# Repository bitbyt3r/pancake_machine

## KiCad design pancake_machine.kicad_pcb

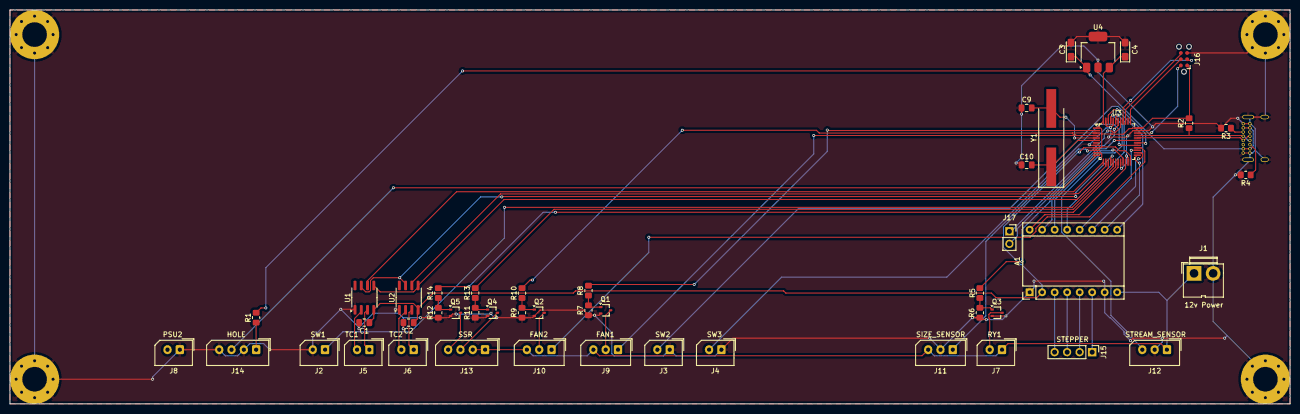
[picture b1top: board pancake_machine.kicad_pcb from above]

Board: 2 copper layers, 260.0 x 80.0 mm, 53 parts (1 on the bottom side), 60 nets.

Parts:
A1: Pololu_Breakout_A4988; Pololu_Breakout-16_15.2x20.3mm
C1, C2: 0.1uF; C_0805_2012Metric_Pad1.18x1.45mm_HandSolder
C3, C4: 10uF; CP_EIA-3216-10_Kemet-I_Pad1.58x1.35mm_HandSolder
C9, C10: 20pF; C_0805_2012Metric_Pad1.18x1.45mm_HandSolder
H2, H3, H4, H5: MountingHole_Pad; MountingHole_5mm_Pad_Via
J1: 12v Power; JWT_A3963_1x02_P3.96mm_Vertical
J2: SW1; Molex_SPOX_5267-02A_1x02_P2.50mm_Vertical
J3: SW2; Molex_SPOX_5267-02A_1x02_P2.50mm_Vertical
J4: SW3; Molex_SPOX_5267-02A_1x02_P2.50mm_Vertical
J5: TC1; Molex_SPOX_5267-02A_1x02_P2.50mm_Vertical
J6: TC2; Molex_SPOX_5267-02A_1x02_P2.50mm_Vertical
J7: RY1; Molex_SPOX_5267-02A_1x02_P2.50mm_Vertical
J8: PSU2; Molex_SPOX_5267-02A_1x02_P2.50mm_Vertical
J9: FAN1; Molex_SPOX_5267-03A_1x03_P2.50mm_Vertical
J10: FAN2; Molex_SPOX_5267-03A_1x03_P2.50mm_Vertical
J11: SIZE_SENSOR; Molex_SPOX_5267-03A_1x03_P2.50mm_Vertical
J12: STREAM_SENSOR; Molex_SPOX_5267-03A_1x03_P2.50mm_Vertical
J13: SSR; Molex_SPOX_5267-04A_1x04_P2.50mm_Vertical
J14: HOLE; Molex_SPOX_5267-04A_1x04_P2.50mm_Vertical
J15: Stepper; PinHeader_1x04_P2.54mm_Vertical
J16: Conn_ARM_SWD_TagConnect_TC2030; Tag-Connect_TC2030-IDC-NL_2x03_P1.27mm_Vertical
J17: Conn_01x02_Socket; PinSocket_1x02_P2.54mm_Vertical
J18: USB_C_Receptacle_USB2.0_14P; USB_C_Receptacle_GCT_USB4085
Q1, Q2, Q3, Q4, Q5: BSS214NW; SOT-323_SC-70
R1: 161; R_0805_2012Metric_Pad1.20x1.40mm_HandSolder
R2: 1k5; R_0805_2012Metric_Pad1.20x1.40mm_HandSolder
R3, R4: 5k1; R_0805_2012Metric_Pad1.20x1.40mm_HandSolder
R5, R8, R10, R13, R14: 100; R_0805_2012Metric_Pad1.20x1.40mm_HandSolder
R6, R7, R9, R11, R12: 100k; R_0805_2012Metric_Pad1.20x1.40mm_HandSolder
U1, U2: MAX31855KASA; SOIC-8_3.9x4.9mm_P1.27mm
U3: STM32F103CBTx; LQFP-48_7x7mm_P0.5mm
U4: LT1963AxST-3.3; SOT-223-3_TabPin2
Y1: 16MHz; Crystal_SMD_HC49-SD_HandSoldering

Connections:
+3.3V: A1.2 (VDD), C1.1, C2.1, C4.1, J16.1 (VCC), R2.2, U1.4 (V_CC), U2.4 (V_CC), U3.1 (VBAT), U3.9 (VDDA), U3.24 (VDD), U3.36 (VDD), U3.48 (VDD), U4.3 (OUT)
+5V: C3.1, J18.A4 (VBUS), J18.A9 (VBUS), J18.B4 (VBUS), J18.B9 (VBUS), R1.2, U4.1 (IN)
+12V: A1.8 (VMOT), J1.1, J7.1, J9.3, J10.3, J11.3, J12.1, J13.1, J13.2
BAG_DOOR_CLOSED: J2.1, U3.17 (PA7)
BELT_MOTOR: R5.1, U3.31 (PA10)
DIAG: J17.2, U3.42 (PB6)
DIR: A1.16 (DIR), U3.22 (PB11)
END_OF_TRAVEL: J3.2, U3.30 (PA9)
FAN1_PWR: R8.2, U3.2 (PC13)
FAN1_SPEED: J9.1, U3.4 (PC15)
FAN2_PWR: R10.2, U3.3 (PC14)
FAN2_SPEED: J10.1, U3.28 (PB15)
GND: A1.1 (GND), A1.7 (GND), C1.2, C2.2, C3.2, C4.2, C9.1, C10.1, H2.1, H3.1, H4.1, H5.1, J1.2, J2.2, J3.1, J4.1, J8.1, J11.2, J12.2, J14.2, J14.4, J16.5 (GND), J18.A1 (GND), J18.A12 (GND), J18.B1 (GND), J18.B12 (GND), J18.S1 (SHIELD), Q1.2 (S), Q2.2 (S), Q3.2 (S), Q4.2 (S), Q5.2 (S), R3.2, R4.2, R6.1, R7.1, R9.1, R11.1, R12.1, U1.1 (GND), U2.1 (GND), U3.8 (VSSA), U3.20 (PB2), U3.23 (VSS), U3.35 (VSS), U3.44 (BOOT0), U3.47 (VSS), U4.2 (GND)
HOLE: J14.3, U3.12 (PA2)
INDEX: J17.1, U3.41 (PB5)
JNTRST: J16.3 (~RESET), U3.40 (PB4)
LOWER_HEATER: R14.2, U3.19 (PB1)
MS1: A1.10 (MS1), U3.25 (PB12)
MS2: A1.11 (MS2), U3.26 (PB13)
MS3: A1.12 (MS3), U3.27 (PB14)
unnamed: A1.4 (1A), J15.3
unnamed: A1.3 (1B), J15.4
unnamed: A1.5 (2A), J15.2
unnamed: A1.6 (2B), J15.1
unnamed: J5.1, U1.3 (T+)
unnamed: J5.2, U1.2 (T-)
unnamed: J6.1, U2.3 (T+)
unnamed: J6.2, U2.2 (T-)
unnamed: J7.2, Q3.3 (D)
unnamed: J9.2, Q1.3 (D)
unnamed: J10.2, Q2.3 (D)
unnamed: J13.3, Q4.3 (D)
unnamed: J13.4, Q5.3 (D)
unnamed: J14.1, R1.1
unnamed: J18.A5 (CC1), R3.1
unnamed: J18.B5 (CC2), R4.1
unnamed: Q1.1 (G), R7.2, R8.1
unnamed: Q2.1 (G), R9.2, R10.1
unnamed: Q3.1 (G), R5.2, R6.2
unnamed: Q4.1 (G), R11.2, R13.1
unnamed: Q5.1 (G), R12.2, R14.1
unnamed: C9.2, U3.5 (PD0), Y1.2
unnamed: C10.2, U3.6 (PD1), Y1.1
SIZE: J11.1, U3.10 (PA0)
SPI_MISO: U1.7 (SO), U2.7 (SO), U3.16 (PA6)
SPI_SCK: U1.5 (SCK), U2.5 (SCK), U3.15 (PA5)
START_OF_TRAVEL: J4.2, U3.29 (PA8)
STEP: A1.15 (STEP), U3.21 (PB10)
STREAM: J12.3, U3.11 (PA1)
SWCLK: J16.4 (SWCLK), U3.37 (PA14)
SWDIO: J16.2 (SWDIO), U3.34 (PA13)
SWO: J16.6 (SWO), U3.39 (PB3)
TC_LOWER: U2.6 (~CS), U3.14 (PA4)
TC_UPPER: U1.6 (~CS), U3.13 (PA3)
UPPER_HEATER: R13.2, U3.18 (PB0)
USB_N: J18.A7 (D-), J18.B7 (D-), U3.32 (PA11)
USB_P: J18.A6 (D+), J18.B6 (D+), R2.1, U3.33 (PA12)
/ENABLE: A1.9 (~ENABLE), U3.46 (PB9)
/RESET: A1.13 (~RESET), U3.43 (PB7)
/SLEEP: A1.14 (~SLEEP), U3.45 (PB8)
